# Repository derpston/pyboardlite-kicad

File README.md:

KiCad design for a minimal PyBoard
--
Like a PyBoard, but sacks off everything unnecessary, like:

* SD card
* Accelerometer
* Second crystal for the RTC
* User button
* Lots of pin headers
* Most of the LEDs

Wait, so what /is/ included?
--

The bare essentials:

* Microcontroller (STM32F405RGT6)
* USB connector
* 3.3v voltage regulator
* Many caps for power supply conditioning
* Reset button
* 8MHz crystal
* An LED for status

Dependencies
--

Some of the parts used are available from [this KiCad part library](https://github.com/derpston/derplib-kicad) and you'll probably need that to make sense of the schematic or make any changes to it.

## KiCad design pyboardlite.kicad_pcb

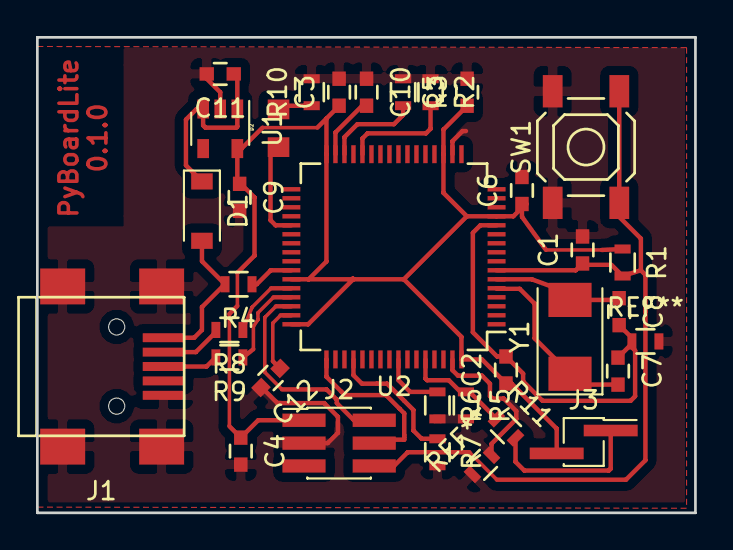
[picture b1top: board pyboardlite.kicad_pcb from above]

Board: 2 copper layers, 36.6 x 26.4 mm, 32 parts (0 on the bottom side), 24 nets.

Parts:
C1, C3, C4, C5, C6: 100nF; C_0603
C2: 4.7uF; C_0603
C7, C8: 18pF; C_0603
C9, C10, C12: 2.2uF; C_0603
C11: 1uF; C_0603
D1: D_Schottky; D_SOD-123
D2: LED_Small; 150080GS75000
J1: USB_OTG; USB_Mini-B
J2: Conn_02x03_Odd_Even; Pin_Header_Straight_2x03_Pitch1.27mm_SMD
J3: DFU_Jumper; Pin_Header_Straight_1x02_Pitch1.27mm_SMD_Pin1Right
R1, R2, R3, R6, R7, R11: 10K; R_0603
R4, R10: 1K; R_0603
R5: 100K; R_0603
R8, R9: 22; R_0603
SW1: Button-PTM; SW_SPST_SKQG
U1: LP2980AIM5-3.3; SOT-23-5
U2: STM32F405RGT6; LQFP-64_10x10mm_Pitch0.5mm
Y1: 8MHz; Crystal_SMD_Abracon_ABM3-2pin_5.0x3.2mm

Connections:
+3V3: C2.1, C3.1, C4.1, C5.1, C6.1, C9.1, J2.1, J3.2, R1.1, U1.5, U2.13, U2.19, U2.32, U2.43, U2.48, U2.64
+5V: C11.1, D1.1, U1.1, U1.3
/NRST: C1.1, J2.6, R1.2, SW1.2, U2.7
/SWCLK: J2.4, U2.49
/SWDIO: J2.2, U2.46
GND: C1.2, C2.2, C3.2, C4.2, C5.2, C6.2, C7.1, C8.2, C9.2, C10.1, C11.2, C12.2, J1.5, J1.6, J2.3, R2.1, R3.1, R5.2, R6.2, R7.2, R10.2, SW1.1, U1.2, U2.12, U2.18, U2.63
unnamed: C7.2, U2.5, Y1.1
unnamed: C8.1, U2.6, Y1.2
unnamed: C10.2, U2.31
unnamed: C12.1, U2.47
unnamed: D1.2, J1.1, R4.2
unnamed: D2.1, R10.1
unnamed: D2.2, U2.37
unnamed: J1.2, R8.2
unnamed: J1.3, R9.2
unnamed: J3.1, R11.2
unnamed: R2.2, U2.28
unnamed: R3.2, U2.30
unnamed: R4.1, U2.42
unnamed: R6.1, U2.57
unnamed: R7.1, U2.52
unnamed: R8.1, U2.44
unnamed: R9.1, U2.45
unnamed: R5.1, R11.1, U2.60

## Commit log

2018-02-19 Initial commit.
2018-02-19 Adding README
2018-02-19 USB connector, SWD header, etc
2018-02-20 Swapped SWD header for a 2x3 1.27mm socket, assigned all footprints.
2018-02-21 Swapping SWD header pin order
2018-02-22 Added LED, did initial board placement and track routing.
2018-02-28 Jiggery pokery
2018-03-04 Adding DFU jumper, moving a jumper resistor, enlarging the board slightly.
